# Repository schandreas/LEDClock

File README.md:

# LEDClock
Swanky LED Clock with modular design and control boards :godmode:

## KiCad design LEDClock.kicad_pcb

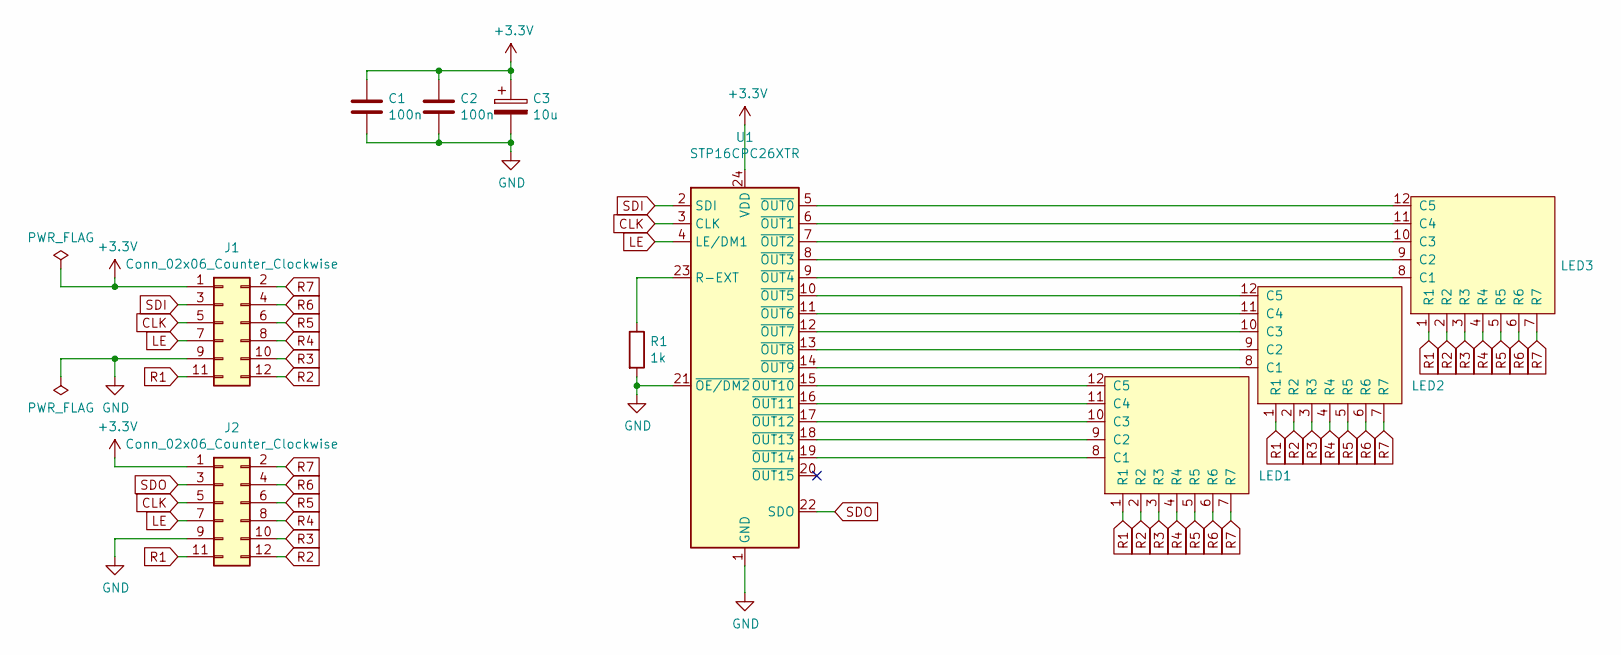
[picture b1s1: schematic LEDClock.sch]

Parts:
C1, C2: 100n; C_1210_3225Metric_Pad1.42x2.65mm_HandSolder; LCSC Number C377122
C3: 10u; CP_Radial_D4.0mm_P2.00mm; LCSC Number C3314
J1: Conn_02x06_Counter_Clockwise; PinSocket_2x06_P2.54mm_Horizontal; LCSC Number C239357
J2: Conn_02x06_Counter_Clockwise; PinHeader_2x06_P2.54mm_Horizontal; LCSC Number C239337
LED1, LED2, LED3: SUNLIGHT_SLDS1357CRA1BD-4.5; LCSC Number C225989
R1: 1k; R_1206_3216Metric_Pad1.42x1.75mm_HandSolder; LCSC Number C1469
U1: STP16CPC26XTR; HTSSOP-24-1EP_4.4x7.8mm_P0.65mm_EP3.2x5mm; LCSC Number C411391

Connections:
+3V3: C1.1, C2.1, C3.1, J1.1, J2.1, U1.24 (VDD)
CLK: J1.5, J2.5, U1.3 (CLK)
GND: C1.2, C2.2, C3.2, J1.9, J2.9, R1.2, U1.1 (GND), U1.21 (~OE/DM2), U1.25 (GND)
LE: J1.7, J2.7, U1.4 (LE/DM1)
unnamed: LED1.8 (C1), U1.19 (~OUT14)
unnamed: LED1.9 (C2), U1.18 (~OUT13)
unnamed: LED1.10 (C3), U1.17 (~OUT12)
unnamed: LED1.11 (C4), U1.16 (~OUT11)
unnamed: LED1.12 (C5), U1.15 (~OUT10)
unnamed: LED2.8 (C1), U1.14 (~OUT9)
unnamed: LED2.9 (C2), U1.13 (~OUT8)
unnamed: LED2.10 (C3), U1.12 (~OUT7)
unnamed: LED2.11 (C4), U1.11 (~OUT6)
unnamed: LED2.12 (C5), U1.10 (~OUT5)
unnamed: LED3.8 (C1), U1.9 (~OUT4)
unnamed: LED3.9 (C2), U1.8 (~OUT3)
unnamed: LED3.10 (C3), U1.7 (~OUT2)
unnamed: LED3.11 (C4), U1.6 (~OUT1)
unnamed: LED3.12 (C5), U1.5 (~OUT0)
unnamed: R1.1, U1.23 (R-EXT)
R1: J1.11, J2.11, LED1.1 (R1), LED2.1 (R1), LED3.1 (R1)
R2: J1.12, J2.12, LED1.2 (R2), LED2.2 (R2), LED3.2 (R2)
R3: J1.10, J2.10, LED1.3 (R3), LED2.3 (R3), LED3.3 (R3)
R4: J1.8, J2.8, LED1.4 (R4), LED2.4 (R4), LED3.4 (R4)
R5: J1.6, J2.6, LED1.5 (R5), LED2.5 (R5), LED3.5 (R5)
R6: J1.4, J2.4, LED1.6 (R6), LED2.6 (R6), LED3.6 (R6)
R7: J1.2, J2.2, LED1.7 (R7), LED2.7 (R7), LED3.7 (R7)
SDI: J1.3, U1.2 (SDI)
SDO: J2.3, U1.22 (SDO)

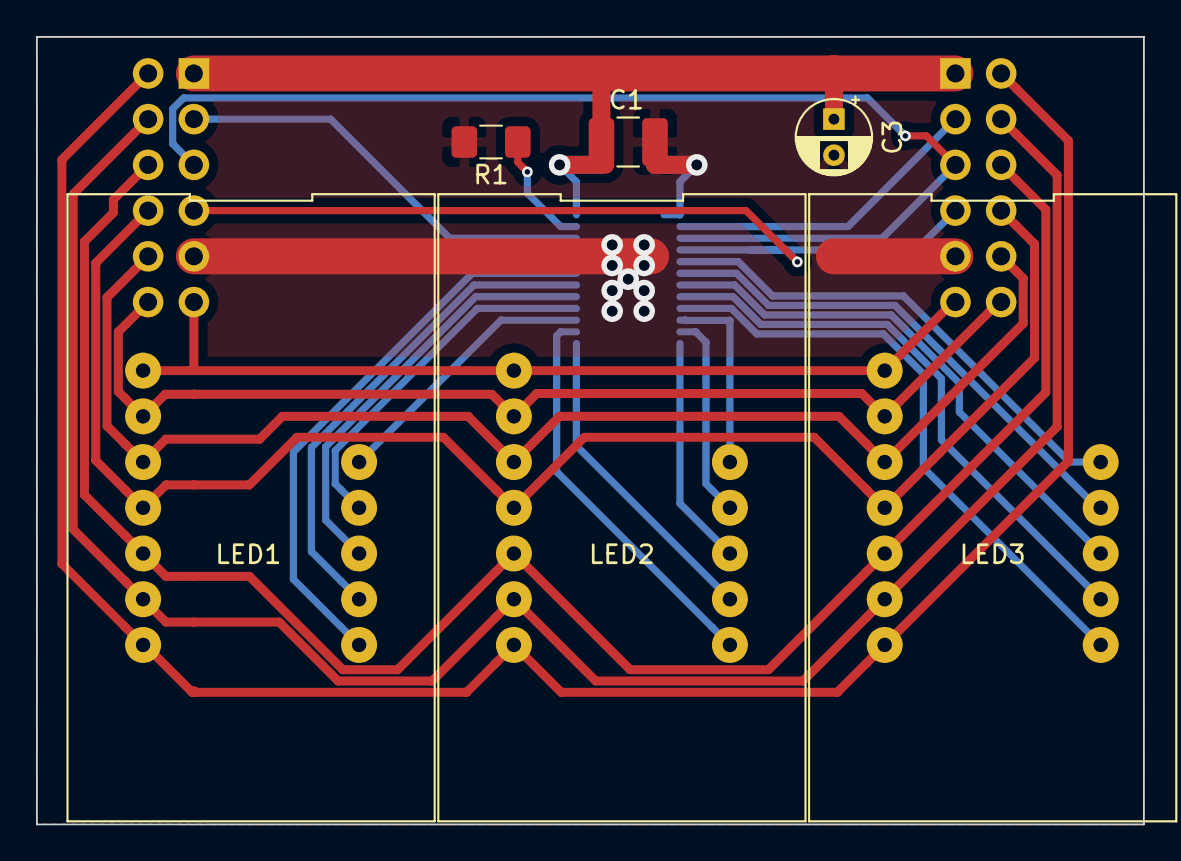
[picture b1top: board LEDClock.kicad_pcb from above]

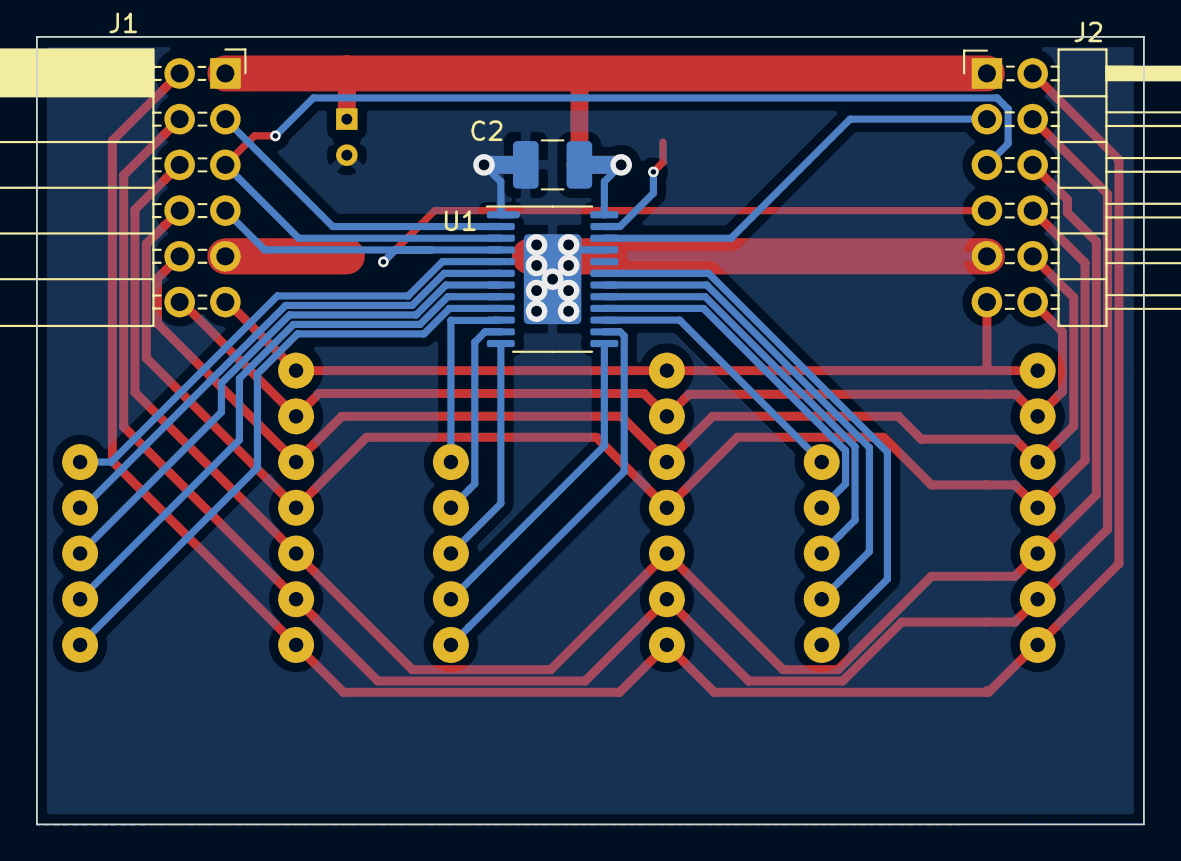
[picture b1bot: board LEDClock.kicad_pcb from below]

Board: 2 copper layers, 61.5 x 43.8 mm, 10 parts (4 on the bottom side), 29 nets.

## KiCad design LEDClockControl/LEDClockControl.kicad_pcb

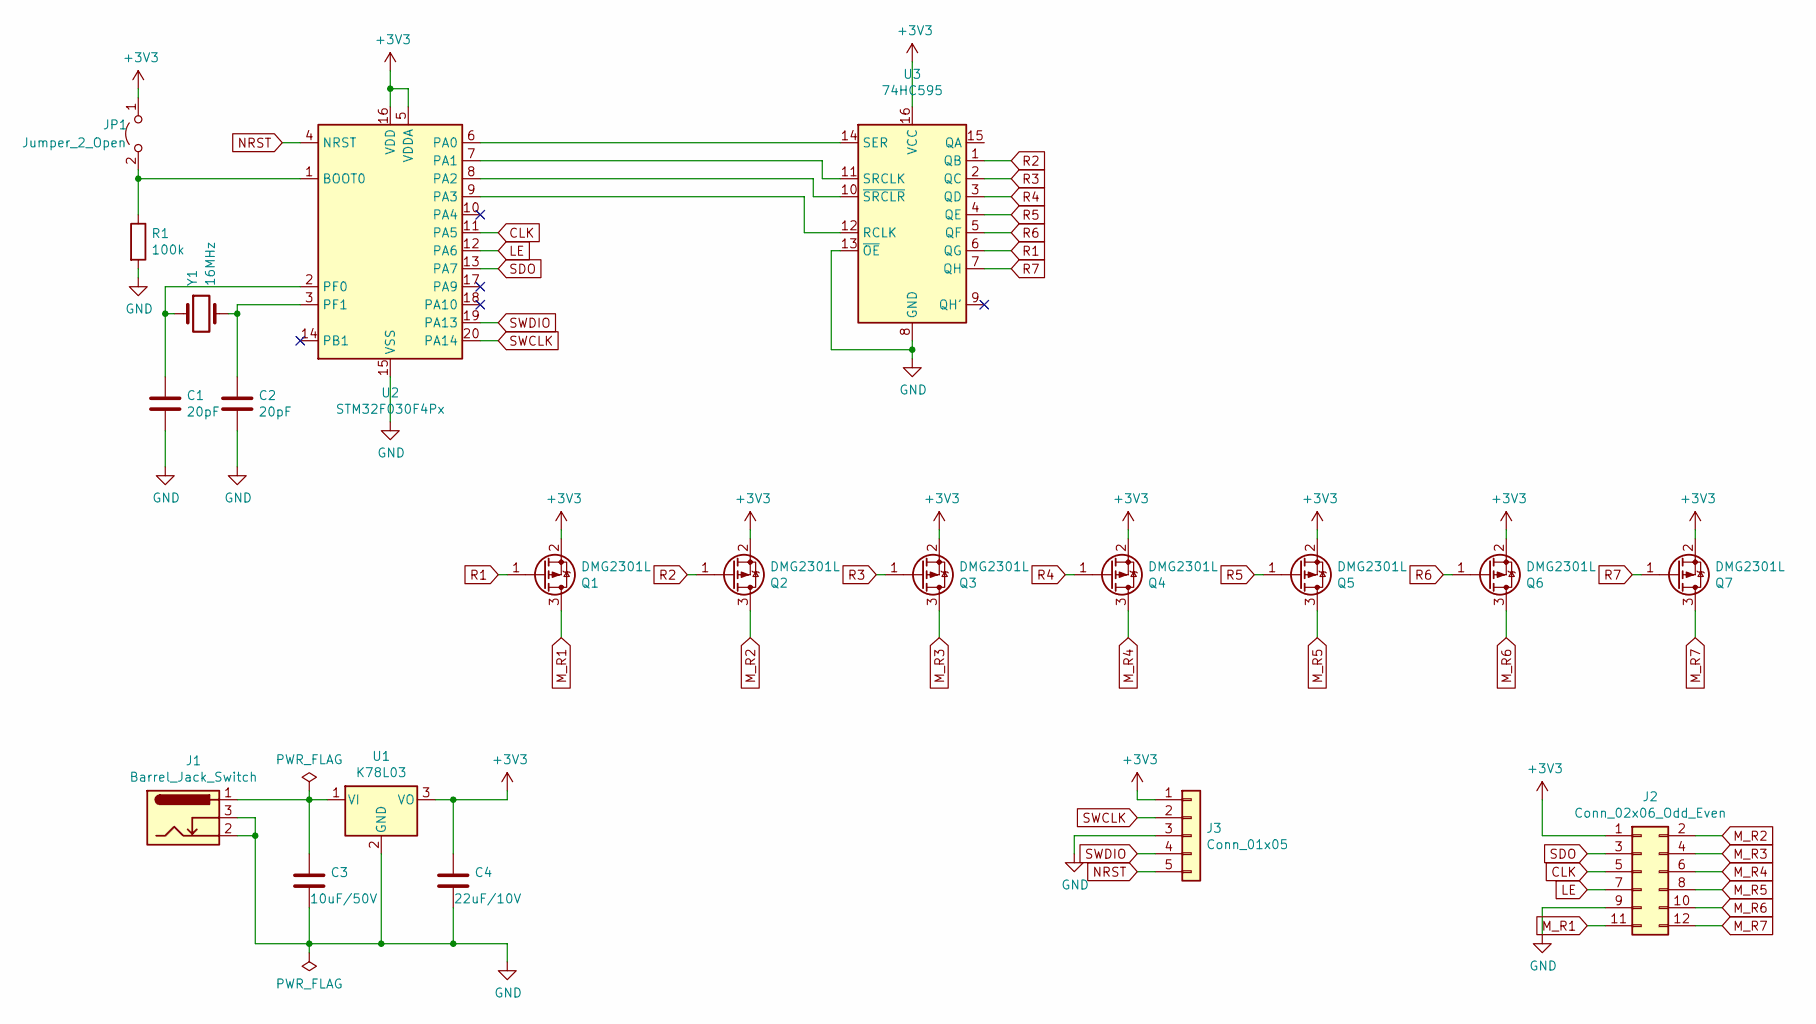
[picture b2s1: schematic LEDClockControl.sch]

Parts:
C1, C2: 20pF; C_1206_3216Metric_Pad1.42x1.75mm_HandSolder; LCSC Number C1886
C3: 10uF/50V; C_1206_3216Metric_Pad1.42x1.75mm_HandSolder; LCSC Number C13585
C4: 22uF/10V; C_1206_3216Metric_Pad1.42x1.75mm_HandSolder; LCSC Number C90146
J1: Barrel_Jack_Switch; BarrelJack_Horizontal; LCSC Number C381116
J2: Conn_02x06_Odd_Even; PinHeader_2x06_P2.54mm_Horizontal; LCSC Number C239337
J3: Conn_01x05; PinHeader_1x05_P2.54mm_Vertical; LCSC Number C358687
JP1: Jumper_2_Open; SolderJumper-2_P1.3mm_Open_Pad1.0x1.5mm
Q1, Q2, Q3, Q4, Q5, Q6, Q7: DMG2301L; SOT-23; LCSC Number C296298
R1: 100k; R_1206_3216Metric_Pad1.42x1.75mm_HandSolder; LCSC Number C127274
U1: K78L03; TO-220-3_Vertical; LCSC Number C115815
U2: STM32F030F4Px; TSSOP-20_4.4x6.5mm_P0.65mm; LCSC Number C32908
U3: 74HC595; SOP-16_4.4x10.4mm_P1.27mm; LCSC Number C87300
Y1: 16MHz; Crystal_HC49-U_Vertical; LCSC Number C16212

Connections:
+3V3: C4.1, J2.1, J3.1, JP1.1 (A), Q1.2 (S), Q2.2 (S), Q3.2 (S), Q4.2 (S), Q5.2 (S), Q6.2 (S), Q7.2 (S), U1.3 (VO), U2.5 (VDDA), U2.16 (VDD), U3.16 (VCC)
CLK: J2.5, U2.11 (PA5)
GND: C1.2, C2.2, C3.2, C4.2, J1.2, J1.3, J2.9, J3.3, R1.2, U1.2 (GND), U2.15 (VSS), U3.8 (GND), U3.13 (~OE)
LE: J2.7, U2.12 (PA6)
M_R1: J2.11, Q1.3 (D)
M_R2: J2.2, Q2.3 (D)
M_R3: J2.4, Q3.3 (D)
M_R4: J2.6, Q4.3 (D)
M_R5: J2.8, Q5.3 (D)
M_R6: J2.10, Q6.3 (D)
M_R7: J2.12, Q7.3 (D)
NRST: J3.5, U2.4 (NRST)
unnamed: C1.1, U2.2 (PF0), Y1.1
unnamed: C2.1, U2.3 (PF1), Y1.2
unnamed: C3.1, J1.1, U1.1 (VI)
unnamed: JP1.2 (B), R1.1, U2.1 (BOOT0)
unnamed: U2.6 (PA0), U3.14 (SER)
unnamed: U2.7 (PA1), U3.11 (SRCLK)
unnamed: U2.8 (PA2), U3.10 (~SRCLR)
unnamed: U2.9 (PA3), U3.12 (RCLK)
R1: Q1.1 (G), U3.6 (QG)
R2: Q2.1 (G), U3.1 (QB)
R3: Q3.1 (G), U3.2 (QC)
R4: Q4.1 (G), U3.3 (QD)
R5: Q5.1 (G), U3.4 (QE)
R6: Q6.1 (G), U3.5 (QF)
R7: Q7.1 (G), U3.7 (QH)
SDO: J2.3, U2.13 (PA7)
SWCLK: J3.2, U2.20 (PA14)
SWDIO: J3.4, U2.19 (PA13)

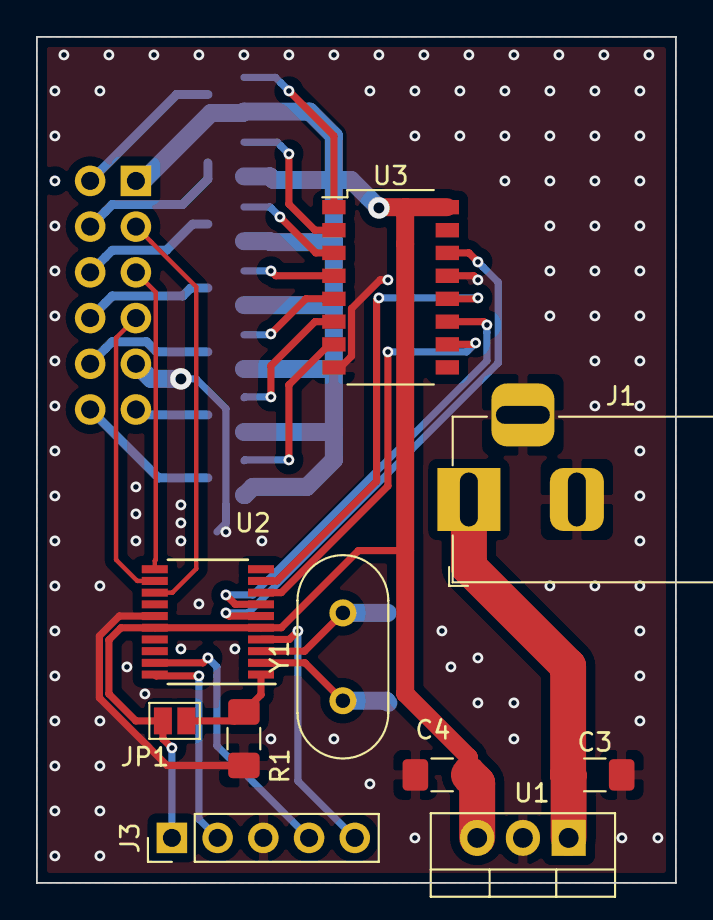
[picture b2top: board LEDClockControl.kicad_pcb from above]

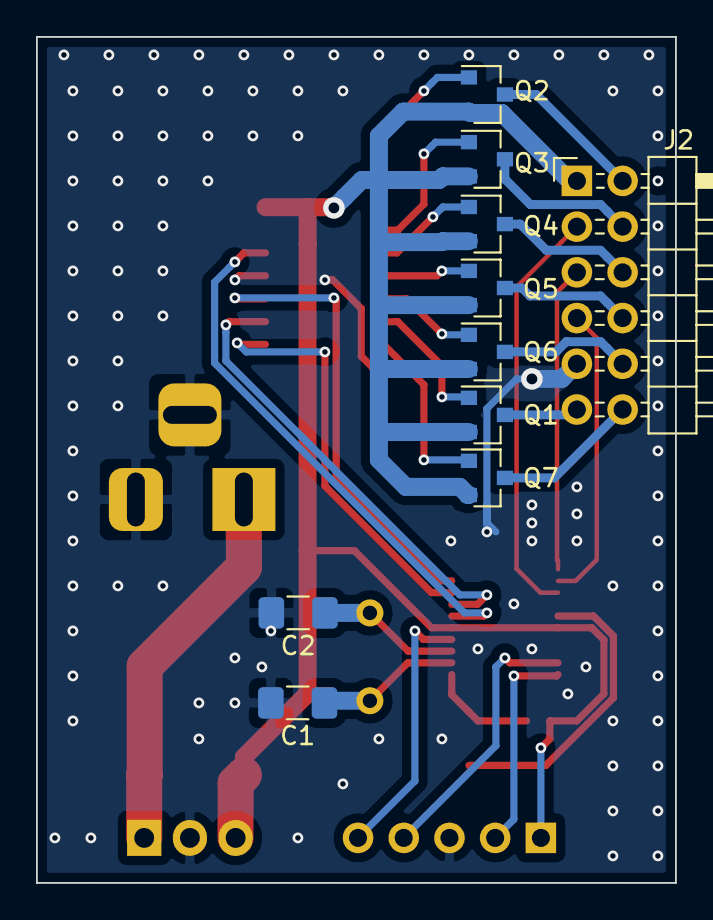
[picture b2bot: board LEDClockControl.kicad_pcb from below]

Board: 2 copper layers, 35.5 x 47.0 mm, 20 parts (10 on the bottom side), 30 nets.

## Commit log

2019-11-21 Initital commit v0.1
2019-11-21 Create LICENSE
2019-11-21 .gitignore fix
2019-11-21 .gitignore number II
2019-11-21 Fixing misc. stuff
    ERC in controll schematic and unused .sch files
2019-11-21 Added RTC to schematic
